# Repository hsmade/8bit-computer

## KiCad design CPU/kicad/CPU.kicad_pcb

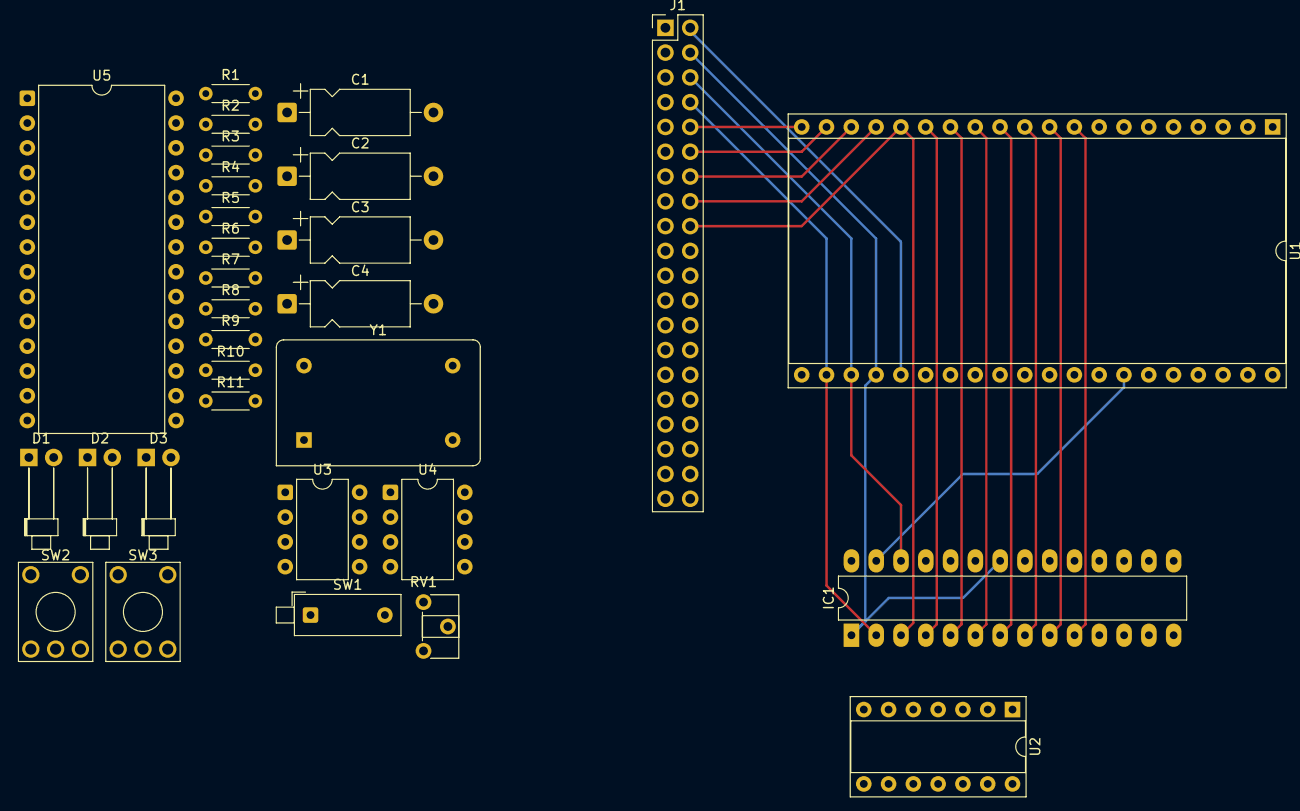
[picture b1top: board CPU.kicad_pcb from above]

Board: 6 copper layers, 30 parts (0 on the bottom side), 49 nets.

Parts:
C1, C3: 10uF; CP_Axial_L10.0mm_D4.5mm_P15.00mm_Horizontal
C2, C4: 103; CP_Axial_L10.0mm_D4.5mm_P15.00mm_Horizontal
D1: Yellow; LED_D1.8mm_W1.8mm_H2.4mm_Horizontal_O6.35mm_Z1.6mm
D2: Red; LED_D1.8mm_W1.8mm_H2.4mm_Horizontal_O6.35mm_Z1.6mm
D3: Blue; LED_D1.8mm_W1.8mm_H2.4mm_Horizontal_O6.35mm_Z1.6mm
IC1: 71256SA20TPGI; DIP-28_W7.62mm_LongPads
J1: Conn_02x20_Odd_Even; PinHeader_2x20_P2.54mm_Vertical
R1: 220; R_Axial_DIN0204_L3.6mm_D1.6mm_P5.08mm_Horizontal
R2, R3, R4, R5, R6, R7, R8, R9: 1k; R_Axial_DIN0204_L3.6mm_D1.6mm_P5.08mm_Horizontal
R10: 1m; R_Axial_DIN0204_L3.6mm_D1.6mm_P5.08mm_Horizontal
R11: 10k; R_Axial_DIN0204_L3.6mm_D1.6mm_P5.08mm_Horizontal
RV1: 1M; Potentiometer_ACP_CA6-H2,5_Horizontal
SW1: SW_DIP_x03; SW_DIP_SPSTx01_Piano_10.8x4.1mm_W7.62mm_P2.54mm
SW2: step; KSA_Tactile_SPST
SW3: reset; KSA_Tactile_SPST
U1: W65C02SxP; DIP-40_W25.4mm_Socket
U2: 74HC00; DIP-14_W7.62mm_Socket
U3, U4: NE555P; DIP-8_W7.62mm
U5: 71256SA20TPGI; DIP-28_W15.24mm
Y1: 1 MHz; Oscillator_DIP-14

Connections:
+5V: D1.2 (A), D2.2 (A), D3.2 (A), J1.33, J1.34, R4.1, R5.1, R6.1, R7.2, R9.1, R10.2, R11.1, SW3.2, U1.8 (VDD), U1.36 (BE), U1.38 (~SO), U2.14 (VCC), U3.4 (R), U3.8 (VCC), U4.4 (R), U4.8 (VCC), U5.28 (VCC), Y1.14 (Vcc)
/A0: IC1.10 (A0), J1.32, U1.9 (A0), U5.10 (A0)
/A1: IC1.9 (A1), J1.30, U1.10 (A1), U5.9 (A1)
/A2: IC1.8 (A2), J1.28, U1.11 (A2), U5.8 (A2)
/A3: IC1.7 (A3), J1.26, U1.12 (A3), U5.7 (A3)
/A4: IC1.6 (A4), J1.24, U1.13 (A4), U5.6 (A4)
/A5: IC1.5 (A5), J1.22, U1.14 (A5), U5.5 (A5)
/A6: IC1.4 (A6), J1.20, U1.15 (A6), U5.4 (A6)
/A7: IC1.3 (A7), J1.18, U1.16 (A7), U5.3 (A7)
/A8: IC1.25 (A8), J1.16, U1.17 (A8), U5.25 (A8)
/A9: IC1.24 (A9), J1.14, U1.18 (A9), U5.24 (A9)
/A10: IC1.21 (A10), J1.12, U1.19 (A10), U5.21 (A10)
/A11: IC1.23 (A11), J1.10, U1.20 (A11), U5.23 (A11)
/A12: IC1.2 (A12), J1.8, U1.22 (A12), U5.2 (A12)
/A13: IC1.26 (A13), J1.6, U1.23 (A13), U5.26 (A13)
/A14: IC1.1 (A14), IC1.22 (~OE), J1.4, R1.1, U1.24 (A14), U5.1 (A14), U5.22 (~OE)
/A15: J1.2, U1.25 (A15), U2.1, U2.2
/D0: IC1.11 (DQ0), J1.1, U1.33 (D0), U5.11 (Q0)
/D1: IC1.12 (DQ1), J1.3, U1.32 (D1), U5.12 (Q1)
/D2: IC1.13 (DQ2), J1.5, U1.31 (D2), U5.13 (Q2)
/D3: IC1.15 (DQ3), J1.7, U1.30 (D3), U5.15 (Q3)
/D4: IC1.16 (DQ4), J1.9, U1.29 (D4), U5.16 (Q4)
/D5: IC1.17 (DQ5), J1.11, U1.28 (D5), U5.17 (Q5)
/D6: IC1.18 (DQ6), J1.13, U1.27 (D6), U5.18 (Q6)
/D7: IC1.19 (DQ7), J1.15, U1.26 (D7), U5.19 (Q7)
/RWb: J1.17, R2.1, U1.34 (R/~W), U5.27 (~WE)
/irq: J1.23, R4.2, U1.4 (~IRQ)
/nmi: J1.25, R5.2, U1.6 (~NMI)
/phi0: J1.37, U1.37 (ϕ0), U2.8
/phi1: J1.21, U1.3 (ϕ1)
/phi2: J1.19, U1.39 (ϕ2), U2.4
/res: J1.27, R6.2, U1.40 (~RES)
GND: C1.2, C2.2, C3.2, C4.1, J1.39, J1.40, SW2.1, SW3.1, U1.21 (VSS), U2.7 (GND), U3.1 (GND), U4.1 (GND), U5.14 (GND), Y1.7 (GND)
unnamed: D1.1 (K), R1.2
unnamed: D2.1 (K), R2.2
unnamed: D3.1 (K), R3.2
unnamed: R8.2, RV1.2
unnamed: U2.9, U2.10
unnamed: R11.2, U1.2 (RDY)
unnamed: U2.3, U2.5
unnamed: C2.1, U3.5 (CV)
unnamed: R7.1, R8.1, U3.7 (DIS)
unnamed: SW1.2, U3.3 (Q)
unnamed: C1.1, RV1.3, U3.2 (TR), U3.6 (THR)
unnamed: C4.2, U4.5 (CV)
unnamed: C3.1, R10.1, U4.6 (THR), U4.7 (DIS)
unnamed: SW1.1, U4.3 (Q)
unnamed: R9.2, SW2.2, U4.2 (TR)
unnamed: R3.1, U2.6, U5.20 (~CS)

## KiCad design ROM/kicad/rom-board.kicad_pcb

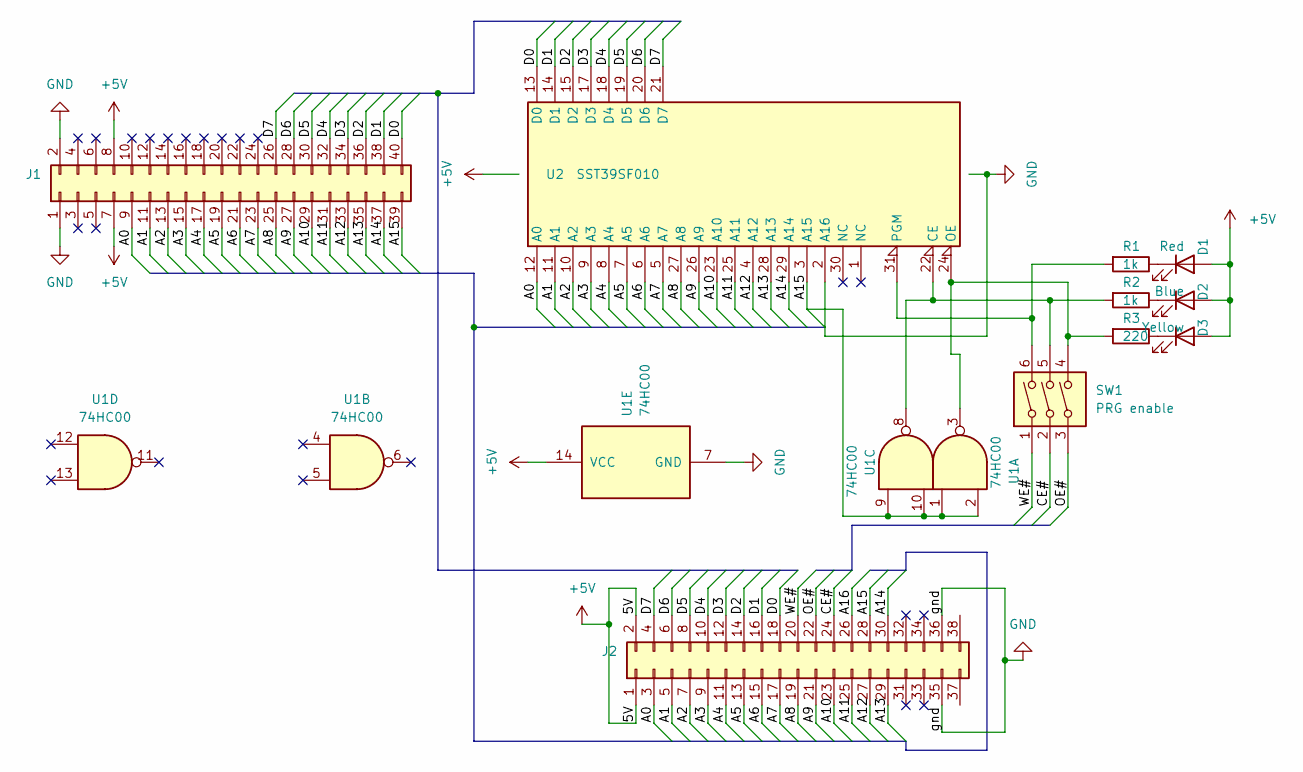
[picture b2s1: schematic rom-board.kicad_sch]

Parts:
D1: Red; LED_D5.0mm
D2: Blue; LED_D5.0mm
D3: Yellow; LED_D5.0mm
J1, J2: (no value)
R1, R2: 1k; R_Axial_DIN0204_L3.6mm_D1.6mm_P2.54mm_Vertical
R3: 220; R_Axial_DIN0204_L3.6mm_D1.6mm_P2.54mm_Vertical
SW1: PRG enable; DIP-6_W7.62mm
U1: 74HC00; DIP-14_W7.62mm
U2: SST39SF010; DIP-32_W15.24mm

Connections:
+5V: D1.2 (A), D2.2 (A), D3.2 (A), J1.7, J1.8, J2.1, J2.2, U1.14 (VCC), U2.32 (VCC)
/A0: J1.9, J2.3, U2.12 (A0)
/A1: J1.11, J2.5, U2.11 (A1)
/A2: J1.13, J2.7, U2.10 (A2)
/A3: J1.15, J2.9, U2.9 (A3)
/A4: J1.17, J2.11, U2.8 (A4)
/A5: J1.19, J2.13, U2.7 (A5)
/A6: J1.21, J2.15, U2.6 (A6)
/A7: J1.23, J2.17, U2.5 (A7)
/A8: J1.25, J2.19, U2.27 (A8)
/A9: J1.27, J2.21, U2.26 (A9)
/A10: J1.29, J2.23, U2.23 (A10)
/A11: J1.31, J2.25, U2.25 (A11)
/A12: J1.33, J2.27, U2.4 (A12)
/A13: J1.35, J2.29, U2.28 (A13)
/A14: J1.37, J2.30, U2.29 (A14)
/A15: J1.39, J2.28, U1.1, U1.2, U1.9, U1.10, U2.3 (A15)
/A16: J2.26
/CE#: J2.24, SW1.2
/D0: J1.40, J2.18, U2.13 (D0)
/D1: J1.38, J2.16, U2.14 (D1)
/D2: J1.36, J2.14, U2.15 (D2)
/D3: J1.34, J2.12, U2.17 (D3)
/D4: J1.32, J2.10, U2.18 (D4)
/D5: J1.30, J2.8, U2.19 (D5)
/D6: J1.28, J2.6, U2.20 (D6)
/D7: J1.26, J2.4, U2.21 (D7)
/OE#: J2.22, SW1.3
/WE#: J2.20, SW1.1
GND: J1.1, J1.2, J2.35, J2.36, U1.7 (GND), U2.2 (A16), U2.16 (GND)
unnamed: D1.1 (K), R1.1
unnamed: D2.1 (K), R2.1
unnamed: D3.1 (K), R3.1
unnamed: R3.2, SW1.4, U1.3, U2.24 (OE)
unnamed: R2.2, SW1.5, U1.8, U2.22 (CE)
unnamed: R1.2, SW1.6, U2.31 (PGM)

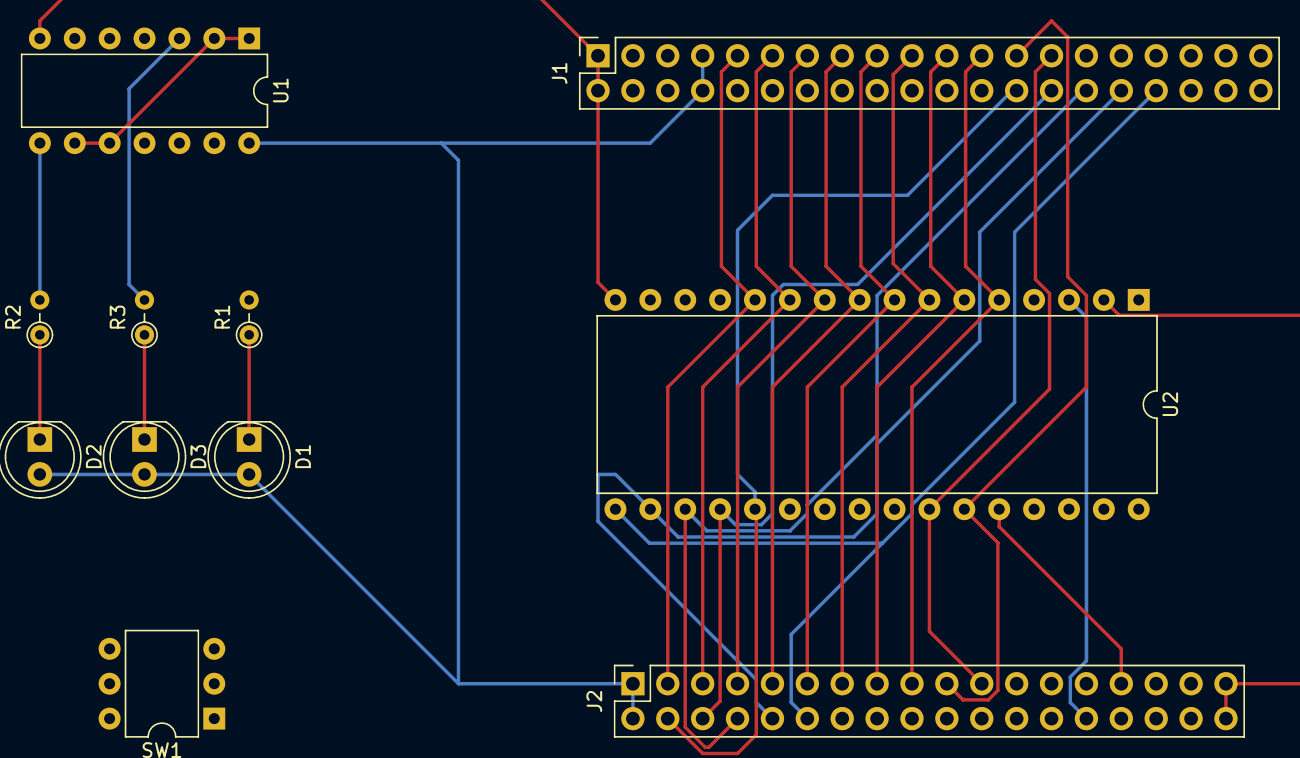
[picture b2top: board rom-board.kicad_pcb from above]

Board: 4 copper layers, 11 parts (0 on the bottom side), 35 nets.

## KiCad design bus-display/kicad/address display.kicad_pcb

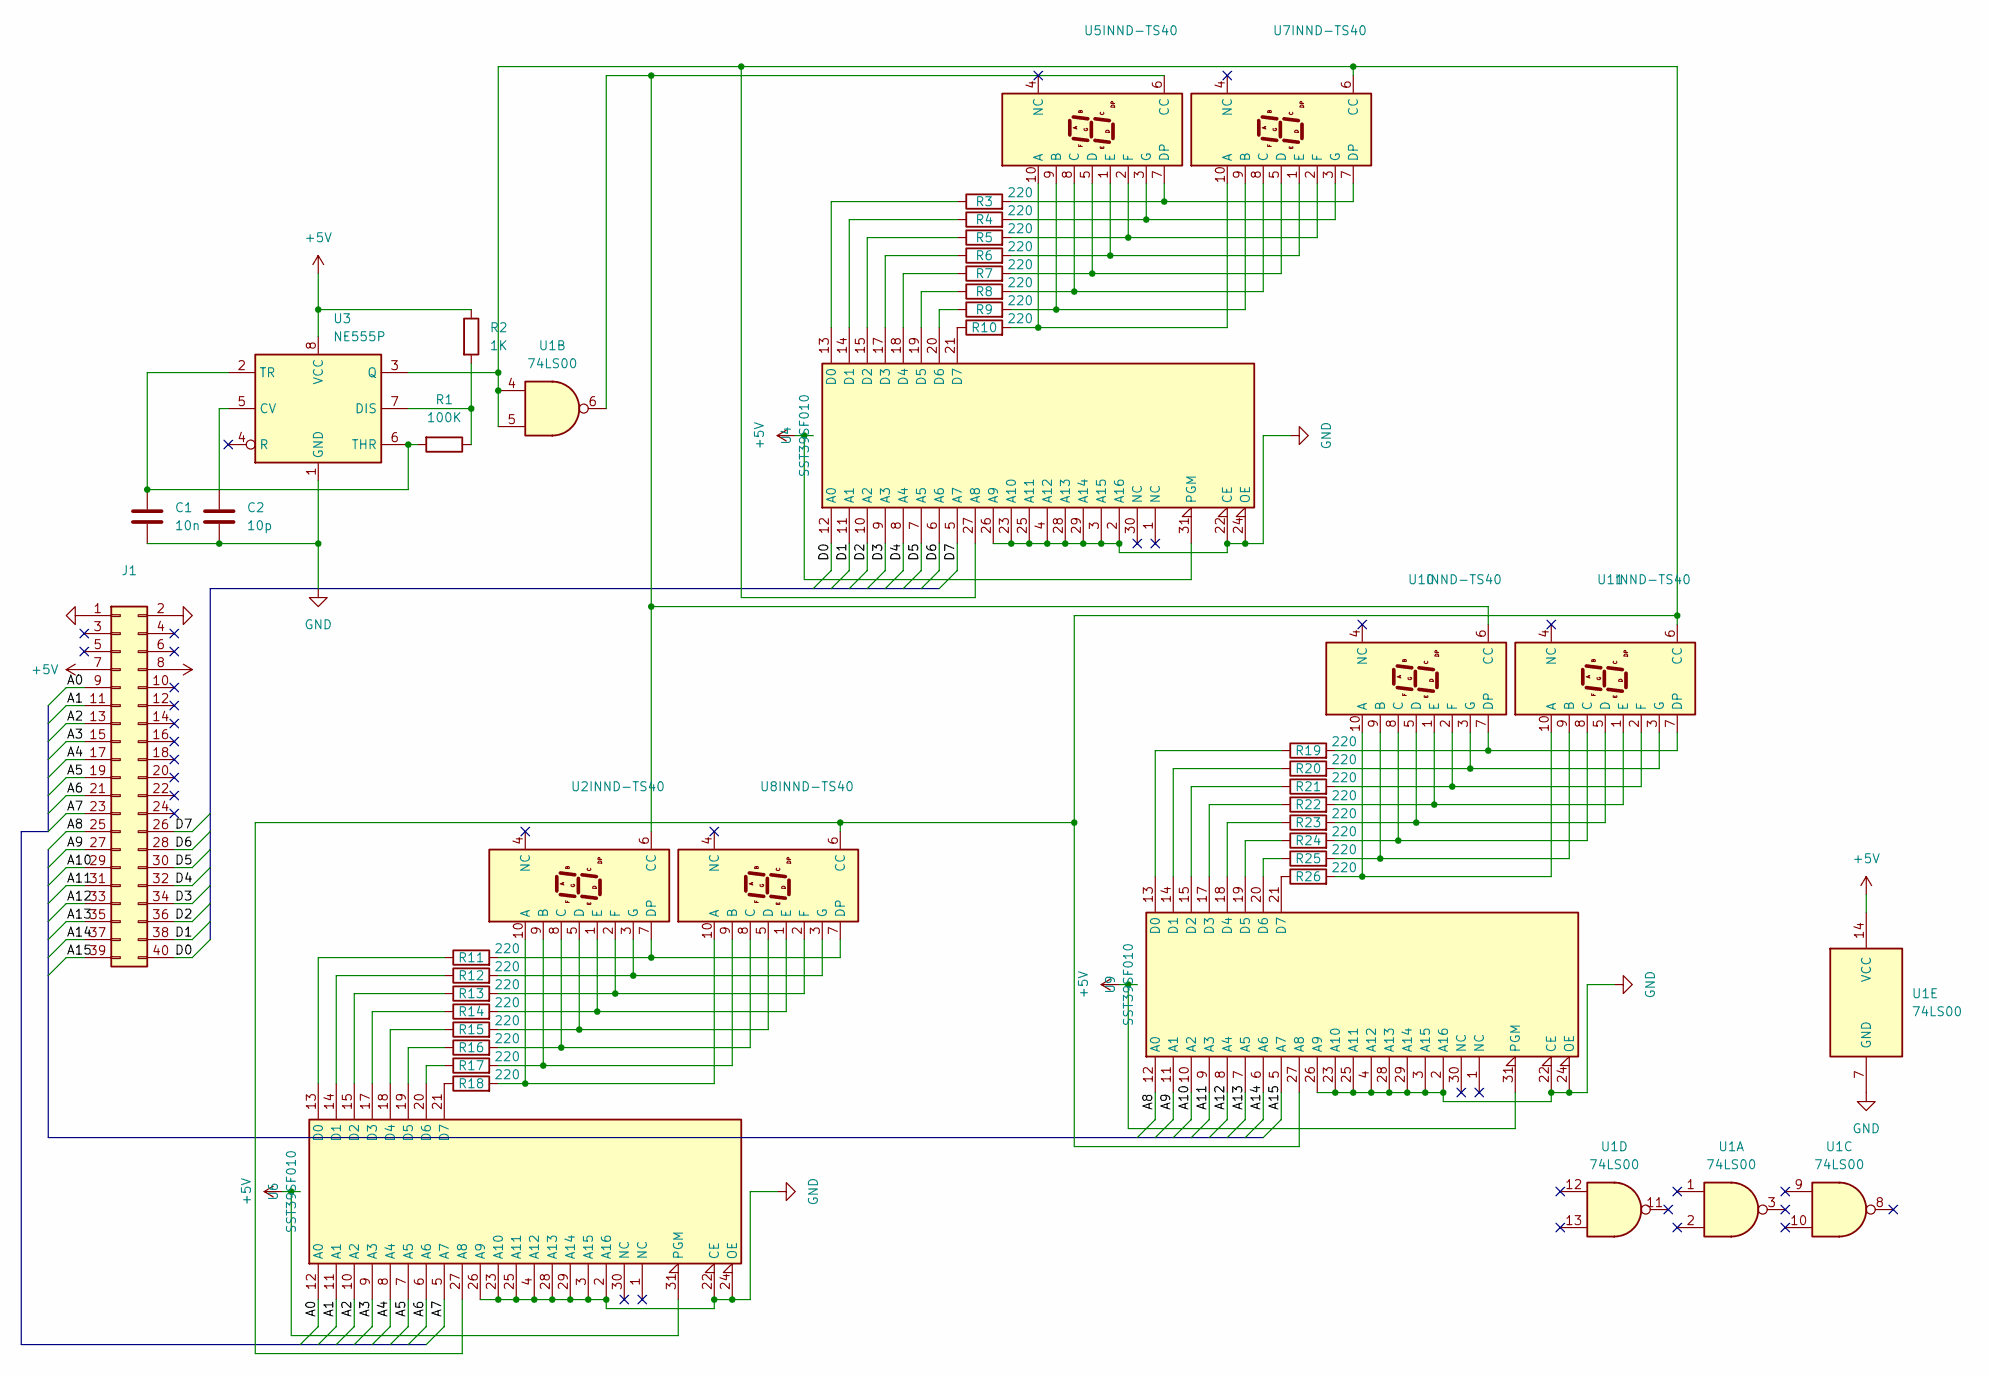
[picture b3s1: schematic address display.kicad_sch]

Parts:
C1: 10n; CP_Radial_Tantal_D4.5mm_P2.50mm
C2: 10p; CP_Radial_Tantal_D4.5mm_P2.50mm
J1: (no value)
R1: 100K; R_Axial_DIN0204_L3.6mm_D1.6mm_P2.54mm_Vertical
R2: 1K; R_Axial_DIN0204_L3.6mm_D1.6mm_P2.54mm_Vertical
R3, R4, R5, R6, R7, R8, R9, R10, R11, R12, R13, R14, R15, R16, R17, R18, R19, R20, R21, R22, R23, R24, R25, R26: 220; R_Axial_DIN0204_L3.6mm_D1.6mm_P2.54mm_Vertical
U1: 74LS00; DIP-14_W7.62mm
U2, U5, U7, U8, U10, U11: INND-TS40
U3: NE555P; DIP-8_W7.62mm
U4, U6, U9: SST39SF010; DIP-32_W15.24mm

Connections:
/A0: J1.9, U6.12 (A0)
/A1: J1.11, U6.11 (A1)
/A2: J1.13, U6.10 (A2)
/A3: J1.15, U6.9 (A3)
/A4: J1.17, U6.8 (A4)
/A5: J1.19, U6.7 (A5)
/A6: J1.21, U6.6 (A6)
/A7: J1.23, U6.5 (A7)
/A8: J1.25, U9.12 (A0)
/A9: J1.27, U9.11 (A1)
/A10: J1.29, U9.10 (A2)
/A11: J1.31, U9.9 (A3)
/A12: J1.33, U9.8 (A4)
/A13: J1.35, U9.7 (A5)
/A14: J1.37, U9.6 (A6)
/A15: J1.39, U9.5 (A7)
/D0: J1.40, U4.12 (A0)
/D1: J1.38, U4.11 (A1)
/D2: J1.36, U4.10 (A2)
/D3: J1.34, U4.9 (A3)
/D4: J1.32, U4.8 (A4)
/D5: J1.30, U4.7 (A5)
/D6: J1.28, U4.6 (A6)
/D7: J1.26, U4.5 (A7)
unnamed: C1.1, R1.2, U3.2 (TR), U3.6 (THR)
unnamed: C2.1, U3.5 (CV)
unnamed: R1.1, R2.2, U3.7 (DIS)
unnamed: R3.2, U5.7 (DP), U7.7 (DP)
unnamed: R4.2, U5.3 (G), U7.3 (G)
unnamed: R5.2, U5.2 (F), U7.2 (F)
unnamed: R6.2, U5.1 (E), U7.1 (E)
unnamed: R7.2, U5.5 (D), U7.5 (D)
unnamed: R8.2, U5.8 (C), U7.8 (C)
unnamed: R9.2, U5.9 (B), U7.9 (B)
unnamed: R10.2, U5.10 (A), U7.10 (A)
unnamed: R11.1, U6.13 (D0)
unnamed: R11.2, U2.7 (DP), U8.7 (DP)
unnamed: R12.1, U6.14 (D1)
unnamed: R12.2, U2.3 (G), U8.3 (G)
unnamed: R13.1, U6.15 (D2)
unnamed: R13.2, U2.2 (F), U8.2 (F)
unnamed: R14.1, U6.17 (D3)
unnamed: R14.2, U2.1 (E), U8.1 (E)
unnamed: R15.1, U6.18 (D4)
unnamed: R15.2, U2.5 (D), U8.5 (D)
unnamed: R16.1, U6.19 (D5)
unnamed: R16.2, U2.8 (C), U8.8 (C)
unnamed: R17.1, U6.20 (D6)
unnamed: R17.2, U2.9 (B), U8.9 (B)
unnamed: R18.1, U6.21 (D7)
unnamed: R18.2, U2.10 (A), U8.10 (A)
unnamed: R19.1, U9.13 (D0)
unnamed: R19.2, U10.7 (DP), U11.7 (DP)
unnamed: R20.1, U9.14 (D1)
unnamed: R20.2, U10.3 (G), U11.3 (G)
unnamed: R21.1, U9.15 (D2)
unnamed: R21.2, U10.2 (F), U11.2 (F)
unnamed: R22.1, U9.17 (D3)
unnamed: R22.2, U10.1 (E), U11.1 (E)
unnamed: R23.1, U9.18 (D4)
unnamed: R23.2, U10.5 (D), U11.5 (D)
unnamed: R24.1, U9.19 (D5)
unnamed: R24.2, U10.8 (C), U11.8 (C)
unnamed: R25.1, U9.20 (D6)
unnamed: R25.2, U10.9 (B), U11.9 (B)
unnamed: R26.1, U9.21 (D7)
unnamed: R26.2, U10.10 (A), U11.10 (A)
unnamed: U1.4, U1.5, U3.3 (Q), U4.27 (A8), U6.27 (A8), U7.6 (CC), U8.6 (CC), U9.27 (A8), U11.6 (CC)
unnamed: R3.1, U4.13 (D0)
unnamed: R4.1, U4.14 (D1)
unnamed: R5.1, U4.15 (D2)
unnamed: R6.1, U4.17 (D3)
unnamed: R7.1, U4.18 (D4)
unnamed: R8.1, U4.19 (D5)
unnamed: R9.1, U4.20 (D6)
unnamed: R10.1, U4.21 (D7)
unnamed: U1.6, U2.6 (CC), U5.6 (CC), U10.6 (CC)

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
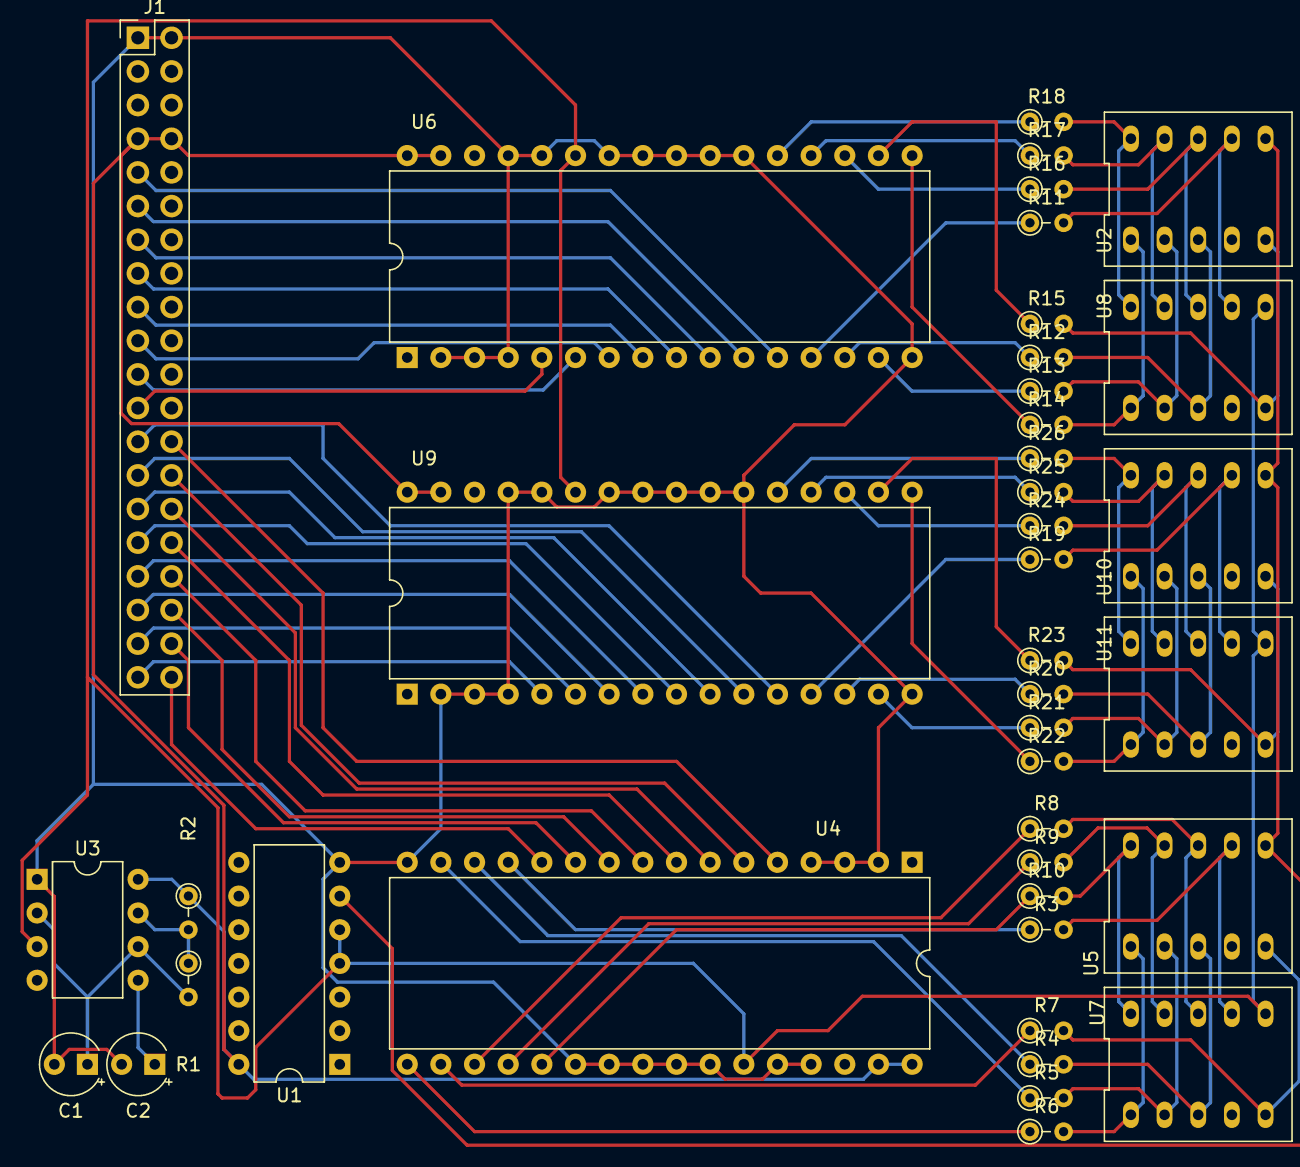
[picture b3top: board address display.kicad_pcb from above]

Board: 2 copper layers, 40 parts (0 on the bottom side), 79 nets.
